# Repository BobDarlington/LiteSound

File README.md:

# LiteSound
This card provides stereo audio capability for the Apple IIGS computers.

This project was done in <b>KiCad 6.0.10</b> and may not work with older versions.

Installation and use manual is a Google Docs file and can be found at this URL:
https://tinyurl.com/39kpvvwv

The J25 header on the IIGS motherboard provides an analog audio signal, and address lines
to drive a demultiplexer which splits audio into Left & Right audio channels.

You can find partially made cables on eBay by searching for 7 pin 2510 or KF2510 cables, 30cm long.  
This length is "about right" and will reach all slots.  Pin 1 on the J25 goes to pin 7 on the LiteSound board.  
This is basically flipped or wired backwards.  Yeah, I should've caught this and may someday fix it.  
It's easy enough to just wire this way!   Included is a closeup photo of both ends of the cable, one end
attached to the PCB, and the other with the alignment tabs for the J25 end clearly visible.

The pins I use are [Molex 16-02-0103](https://www.mouser.com/ProductDetail/538-16-02-0103) on the LightSound end,
and the housings are [Molex 50-57-9207](https://www.mouser.com/ProductDetail/538-50-57-9207).

I'm using a [74HC4052D](https://www.digikey.com/en/products/detail/toshiba-semiconductor-and-storage/74HC4052D/6109174) demultiplexer
and a [TL074CDR](https://www.digikey.com/en/products/detail/texas-instruments/TL074CDR/276926) quad audio op-amp.  There are other pin-compatible
chips that can be substituted.

The headphone jack I use is a [CUI Devices SJ1-3515N](https://www.mouser.com/ProductDetail/490-SJ1-3515N) and the
7 pin header is an [Amphenol 77315-124-07LF](https://www.mouser.com/ProductDetail/649-77315-124-07LF).

Current(ish) board rendering:
[PCB rendering](IIGS-audio.png)

This rendering shows a 2 pin header that was added at the request of about two people who wanted the ability to power this board externally.   
This is not the norm, but you <B>can</b> do it if you really want to.  It's your GS, you do with it as you please!  This doesn't mean external to
the case, just external to the slot (with +/-5v wires run to the pcb) so you don't have to tie up a slot.   This is on you to figure out
how to do.  The only ground on this board is the analog ground on the J25 header on the motherboard.  Don't tie analog ground to digital ground 
(it says so right on the GS schematic).   This will introduce noise, as will decoupling capacitors between +/-5v and digital ground.  That's
why they're not on the board.

This is technically the 4th revision of the PCB.   1st rev worked fine, but was too short for PCBWay to be able to bevel the card edge.   2nd rev was bigger with some
parts moved around where it would be natural to accidentally pull the audio coupling capacitors off the board.  Initially I was using low profile SMT tantalum capacitors for this.
People had a real problem with the idea of using tants so I switched to the SMT electrolytic caps.  3rd rev moved those caps to where they are now,
but also included coupling caps for the power supplies to DC ground.  I learned the hard way not to do this.  Don't do it.   Noise will be introduced.
4th rev removed those two capacitors and added the two pin header.

<b>Known issue:</b> This stereo sound card makes a chirp / squawk sound when the IIGS is switched off if a Reactive Mircro power supply is installed.   This does not happen
if your system uses an original power supply and does not impact performance in any way.  It may do the same with other aftermarket power supplies. YMMV.

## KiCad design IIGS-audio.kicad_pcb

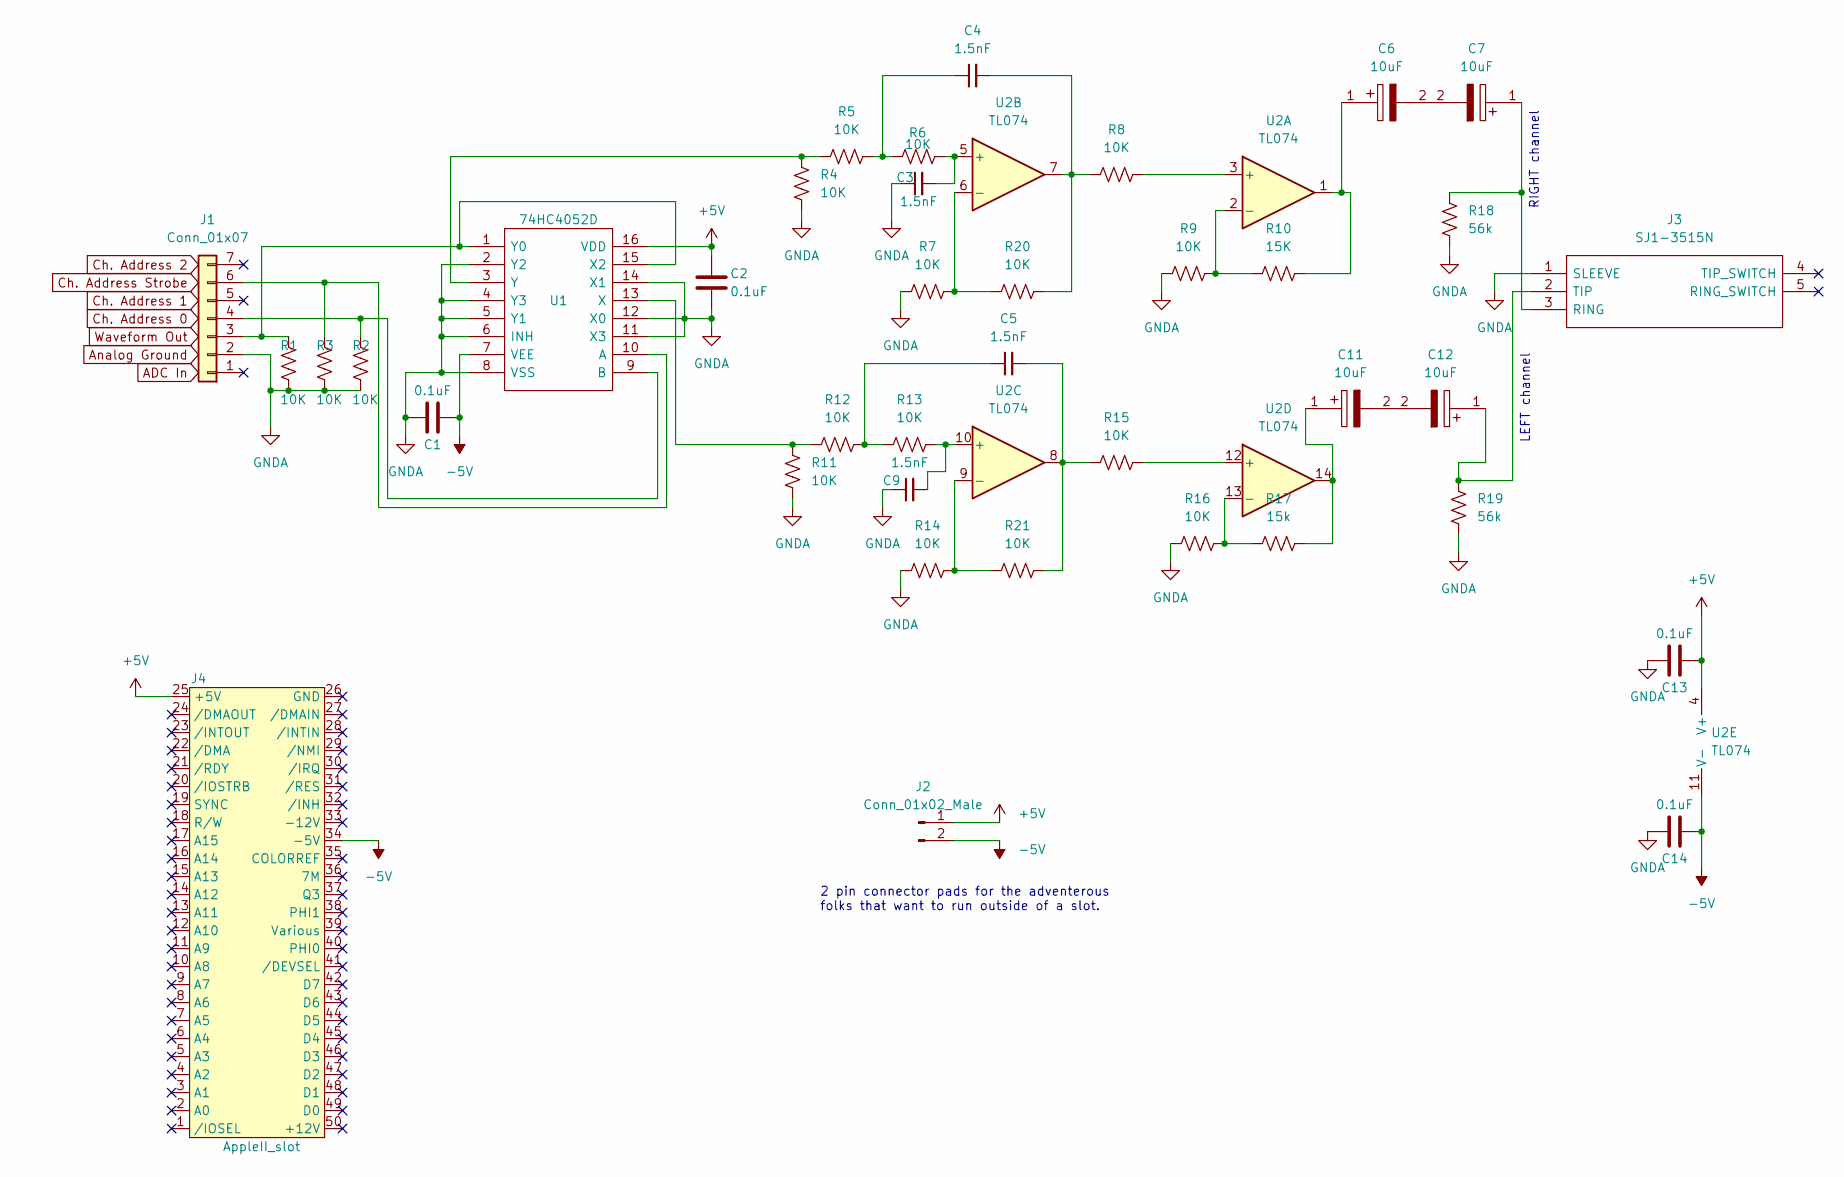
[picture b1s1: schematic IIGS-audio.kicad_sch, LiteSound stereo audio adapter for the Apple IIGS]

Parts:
C1, C2, C13, C14: 0.1uF; C_0603_1608Metric
C3, C4, C5, C9: 1.5nF; C_0603_1608Metric
C6, C7, C11, C12: 10uF; CAPAE430X610N; Mouser Part Number 140-VZT100M1HTR-0406
J1: Conn_01x07; PinHeader_1x07_P2.54mm_Horizontal
J2: Conn_01x02_Male; PinHeader_1x02_P2.54mm_Vertical
J3: SJ1-3515N; SJ13515N; Mouser Part Number 490-SJ1-3515N
J4: AppleII_slot; Apple2_card_slot
R1, R2, R3, R4, R5, R6, R7, R8, R9, R11, R12, R13, R14, R15, R16, R20, R21: 10K; R_0603_1608Metric
R10: 15K; R_0603_1608Metric
R17: 15k; R_0603_1608Metric
R18, R19: 56k; R_0603_1608Metric
U1: 74HC4052D; SOIC127P600X175-16N; Manufacturer_Part_Number MC14052BDR2G; Mouser Part Number 863-MC14052BDR2G
U2: TL074; SOIC-14_3.9x8.7mm_P1.27mm

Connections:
+5V: C2.1, C13.2, J2.1, J4.25 (+5V), U1.16 (VDD), U2.4 (V+)
-5V: C1.2, C14.2, J2.2, J4.34 (-5V), U1.7 (VEE), U2.11 (V-)
GNDA: C1.1, C2.2, C3.1, C9.1, C13.1, C14.1, J1.2, J3.1 (SLEEVE), R1.1, R2.1, R3.1, R4.1, R7.2, R9.2, R11.1, R14.2, R16.2, R18.1, R19.1, U1.2 (Y2), U1.4 (Y3), U1.5 (Y1), U1.6 (INH), U1.8 (VSS), U1.11 (X3), U1.12 (X0), U1.14 (X1)
unnamed: C3.2, R6.2, U2.5 (+)
unnamed: C4.1, R5.2, R6.1
unnamed: C4.2, R8.1, R20.1, U2.7
unnamed: C5.1, R12.2, R13.1
unnamed: C5.2, R15.1, R21.1, U2.8
unnamed: C6.1, R10.2, U2.1
unnamed: C6.2, C7.2
unnamed: C7.1, J3.3 (RING), R18.2
unnamed: C9.2, R13.2, U2.10 (+)
unnamed: C11.1, R17.2, U2.14
unnamed: C11.2, C12.2
unnamed: C12.1, J3.2 (TIP), R19.2
unnamed: J1.3, R1.2, U1.1 (Y0), U1.15 (X2)
unnamed: J1.4, R2.2, U1.9 (B)
unnamed: J1.6, R3.2, U1.10 (A)
unnamed: R4.2, R5.1, U1.3 (Y)
unnamed: R8.2, U2.3 (+)
unnamed: R9.1, R10.1, U2.2 (-)
unnamed: R11.2, R12.1, U1.13 (X)
unnamed: R14.1, R21.2, U2.9 (-)
unnamed: R15.2, U2.12 (+)
unnamed: R16.1, R17.1, U2.13 (-)
unnamed: R7.1, R20.2, U2.6 (-)

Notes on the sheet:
2 pin connector pads for the adventerous folks that want to run outside of a slot.
LEFT channel
RIGHT channel

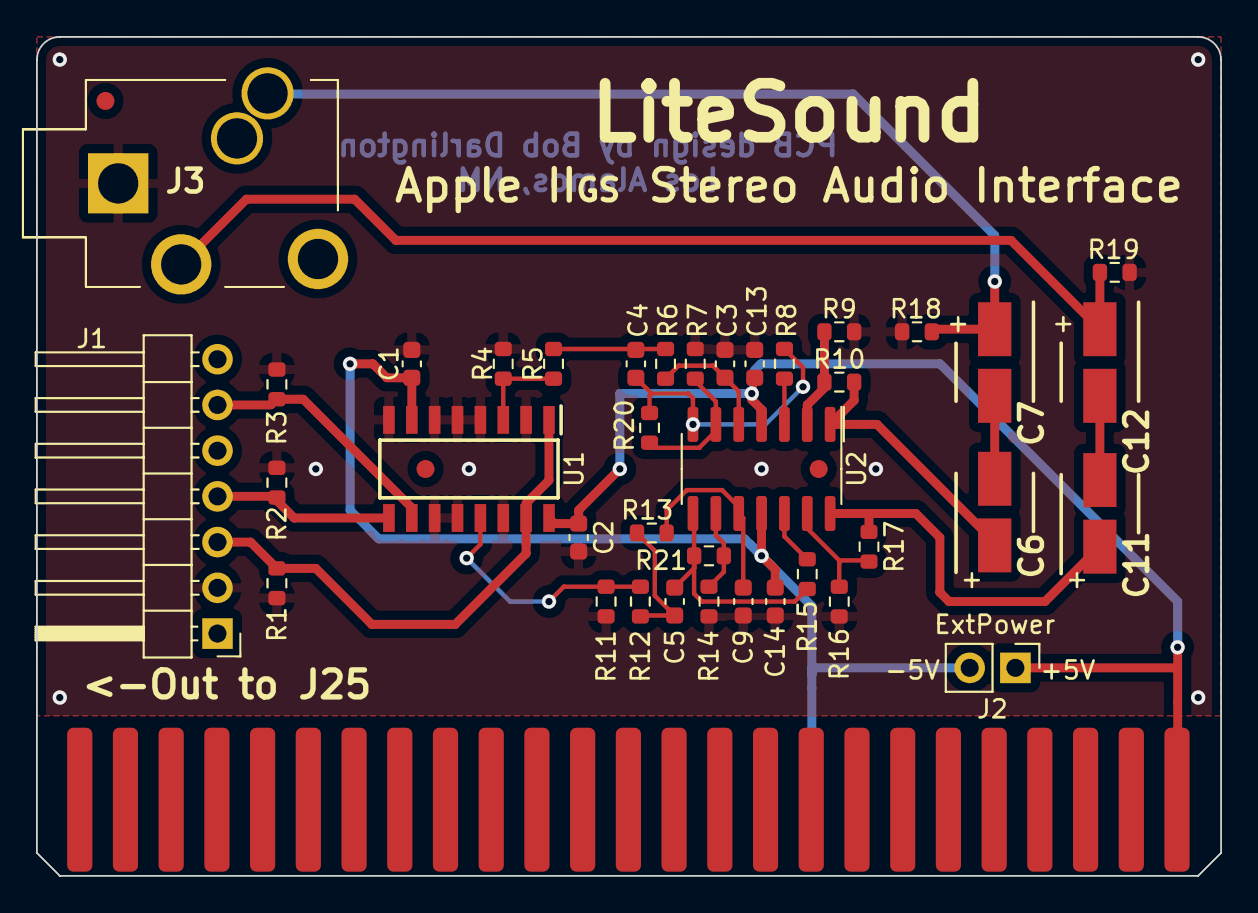
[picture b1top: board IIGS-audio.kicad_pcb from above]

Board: 2 copper layers, 65.8 x 46.6 mm, 42 parts (0 on the bottom side), 26 nets.

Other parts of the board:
REF01, REF02, REF03: Fiducial_1mm_Mask2mm

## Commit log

2022-07-12 Initial upload of files
2022-07-12 Add license
2022-07-12 Added specific parts used on the PCB
2022-07-15 minor tweaks, got rid of PSU rail caps because they contributed to noise
2022-07-15 Current layout rendering
2022-07-15 Added PCB rendering and updated README.md
2022-07-15 Added in dot files
2022-07-15 Updated the PCB image
2022-07-15 Removed some junk files
2022-07-15 Updated the .gitignore
2022-07-16 Updated to reflect current layout.
2022-07-26 Added a blurb about aftermarket power supplies
2022-07-26 Updated readme to include information about aftermarket power supplies
2022-07-26 Upgraded KiCad
2022-07-26 Update README.md
    Rev'd the KiCad version number
2022-07-26 Changed silkscreen label from J-25 to J25 to match the IIGS motherboard
2022-07-26 Changed silkscreen label from J-25 to J25 to match IIGS motherboard
2022-07-26 Updated rendering to match current PCB rev.
2022-07-26 Formatting and additional information.
2022-08-02 Latest rendering
2022-08-02 Minor layout tweaks.
2022-08-02 Minor tweaks to layout
2022-08-03 Exploring fiducial markers
2022-08-03 Added fiducial markers for pick and place machines.
2022-08-03 Adjusted fiducials for PnP machines. Hid them under components.
2022-08-04 Excluded the gerber ouput directory
2022-09-25 Changed the output directory name for gerber files.
2022-09-25 Added a URL to the user manual
2022-12-29 Updated fiducial markers
2022-12-29 Set origin and upgraded to KiCAD 6.0.10
2022-12-29 Reved the KiCAD version number
2024-09-03 Added a photo of the cable so folks can wire it correctly to the J25 connector on the mobo.
2024-09-03 Added part numbers and info about the cable and corrected spelling.
2024-09-03 Added some revision history information.
2025-05-14 Update README.md
    Added a photo to the README.md file
2025-05-14 Update README.md
    Better picture of the card to go inline.
2025-11-09 Delete LICENSE.md
    Changing to Unlicense. Do as you please.
2025-11-09 Update license
